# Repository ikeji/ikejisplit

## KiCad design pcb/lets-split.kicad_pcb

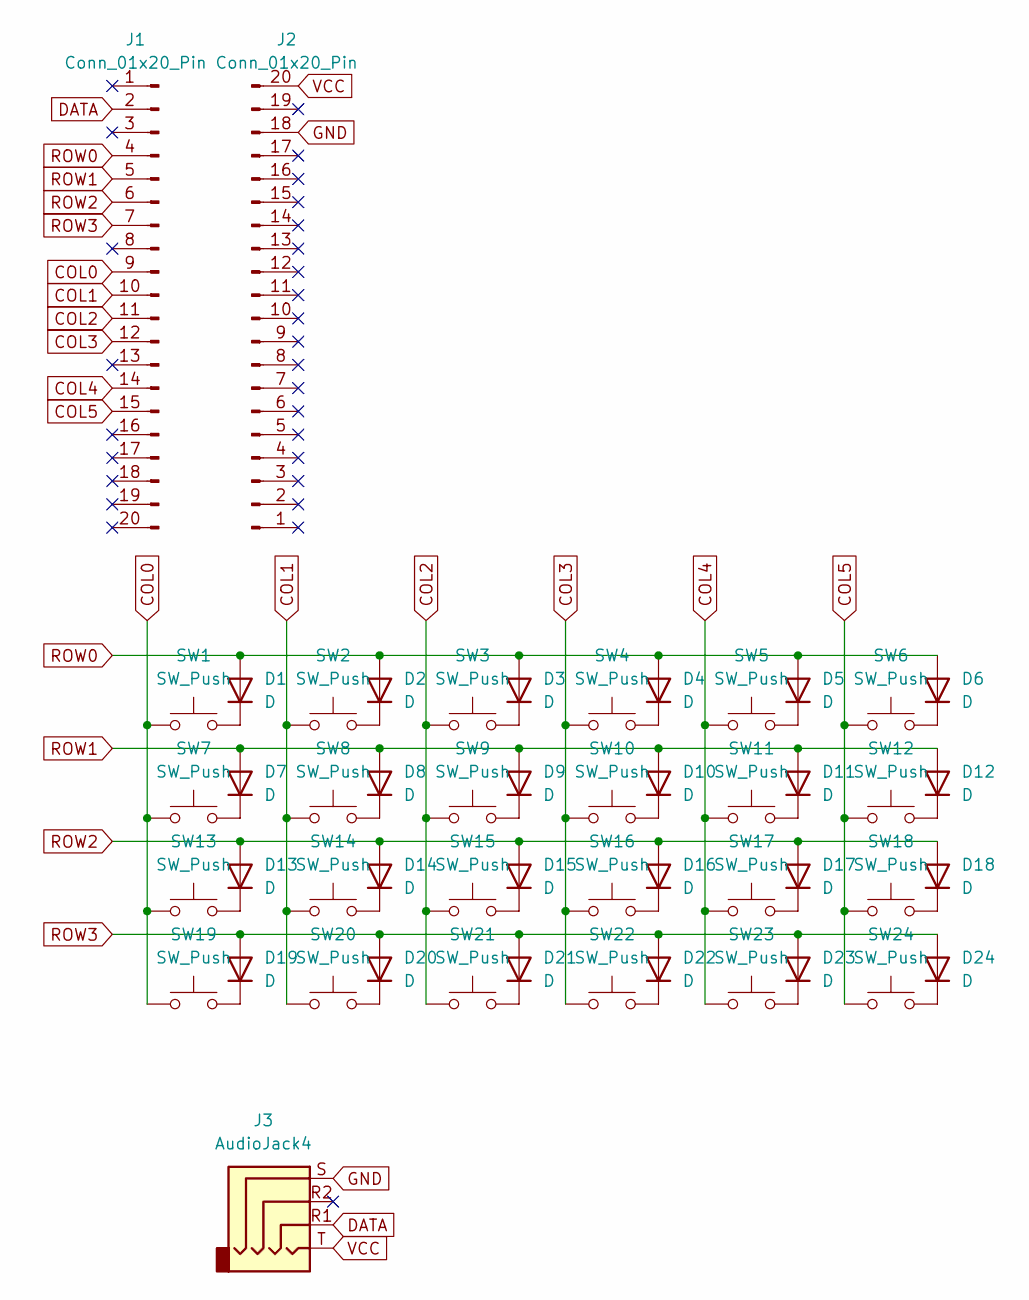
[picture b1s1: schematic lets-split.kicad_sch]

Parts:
D1, D2, D3, D4, D5, D6, D7, D8, D9, D10, D11, D12, D13, D14, D15, D16, D17, D18, D19, D20, D21, D22, D23, D24: D; D_DO-34_SOD68_P7.62mm_Horizontal
J1, J2: Conn_01x20_Pin; PinHeader_1x20_P2.54mm_Vertical
J3: AudioJack4; Jack_3.5mm_PJ320E_Horizontal
SW1, SW2, SW3, SW4, SW5, SW6, SW7, SW8, SW9, SW10, SW11, SW12, SW13, SW14, SW15, SW16, SW17, SW18, SW19, SW20, SW21, SW22, SW23, SW24: SW_Push; SW_Cherry_MX_1.00u_PCB

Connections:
COL0: J1.9, SW1.1, SW7.1, SW13.1, SW19.1
COL1: J1.10, SW2.1, SW8.1, SW14.1, SW20.1
COL2: J1.11, SW3.1, SW9.1, SW15.1, SW21.1
COL3: J1.12, SW4.1, SW10.1, SW16.1, SW22.1
COL4: J1.14, SW5.1, SW11.1, SW17.1, SW23.1
COL5: J1.15, SW6.1, SW12.1, SW18.1, SW24.1
DATA: J1.2, J3.R1
GND: J2.18, J3.S
unnamed: D1.1 (K), SW1.2
unnamed: D2.1 (K), SW2.2
unnamed: D3.1 (K), SW3.2
unnamed: D4.1 (K), SW4.2
unnamed: D5.1 (K), SW5.2
unnamed: D6.1 (K), SW6.2
unnamed: D7.1 (K), SW7.2
unnamed: D8.1 (K), SW8.2
unnamed: D9.1 (K), SW9.2
unnamed: D10.1 (K), SW10.2
unnamed: D11.1 (K), SW11.2
unnamed: D12.1 (K), SW12.2
unnamed: D13.1 (K), SW13.2
unnamed: D14.1 (K), SW14.2
unnamed: D15.1 (K), SW15.2
unnamed: D16.1 (K), SW16.2
unnamed: D17.1 (K), SW17.2
unnamed: D18.1 (K), SW18.2
unnamed: D19.1 (K), SW19.2
unnamed: D20.1 (K), SW20.2
unnamed: D21.1 (K), SW21.2
unnamed: D22.1 (K), SW22.2
unnamed: D23.1 (K), SW23.2
unnamed: D24.1 (K), SW24.2
ROW0: D1.2 (A), D2.2 (A), D3.2 (A), D4.2 (A), D5.2 (A), D6.2 (A), J1.4
ROW1: D7.2 (A), D8.2 (A), D9.2 (A), D10.2 (A), D11.2 (A), D12.2 (A), J1.5
ROW2: D13.2 (A), D14.2 (A), D15.2 (A), D16.2 (A), D17.2 (A), D18.2 (A), J1.6
ROW3: D19.2 (A), D20.2 (A), D21.2 (A), D22.2 (A), D23.2 (A), D24.2 (A), J1.7
VCC: J2.20, J3.T

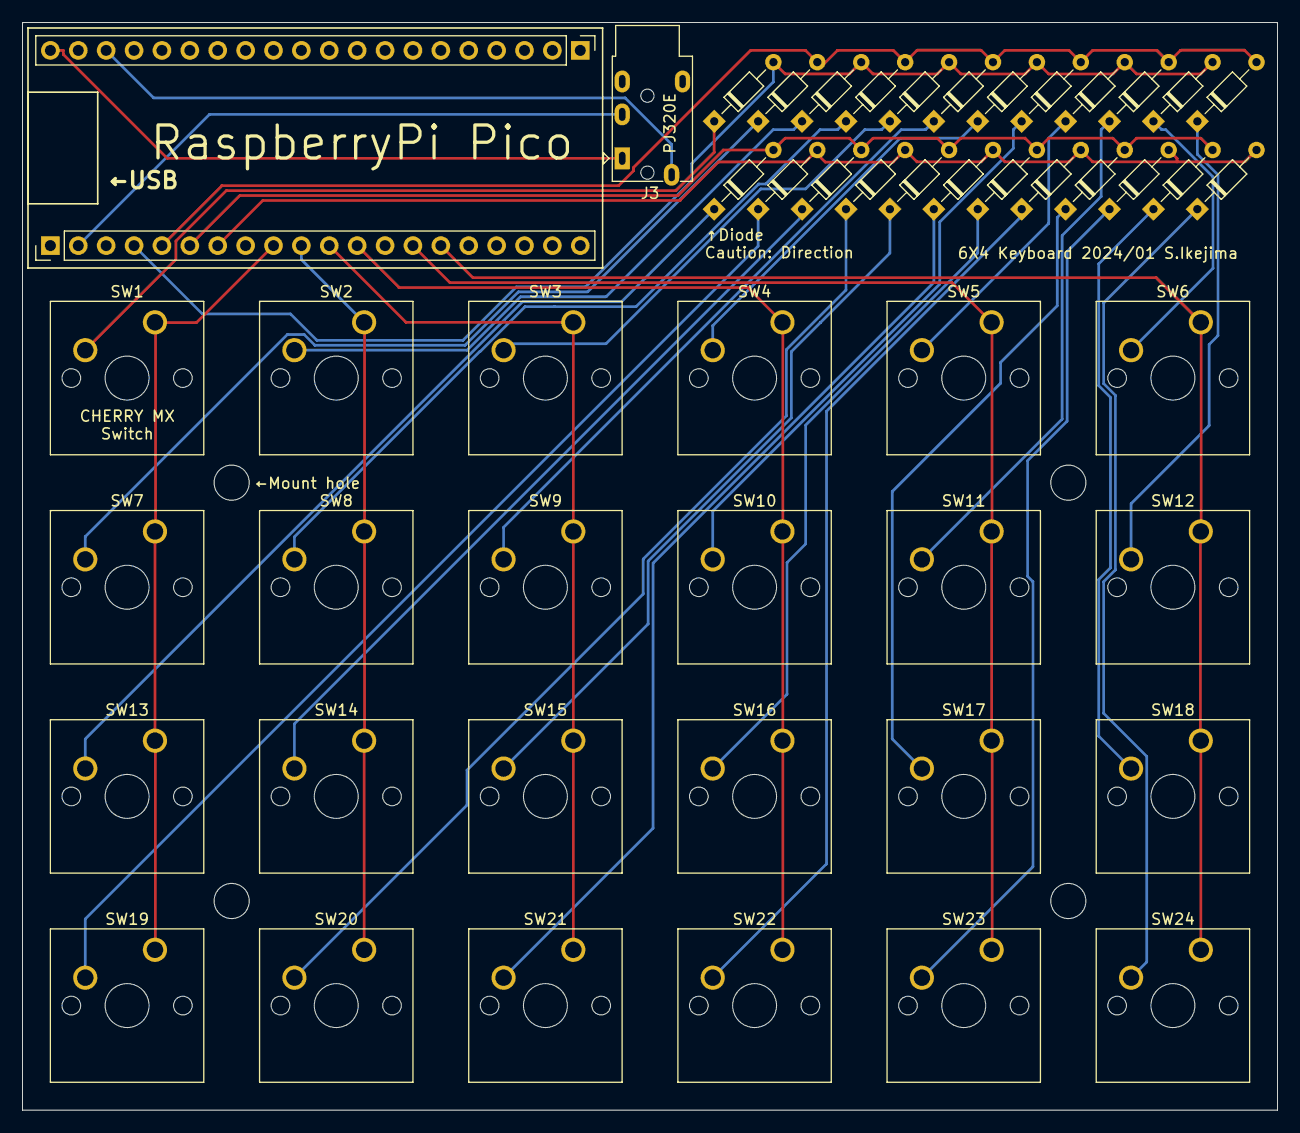
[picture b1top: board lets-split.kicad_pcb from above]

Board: 2 copper layers, 114.3 x 99.1 mm, 55 parts (0 on the bottom side), 37 nets.

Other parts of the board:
REF1, REF2, REF3, REF4: MountingHole_3.2mm_M3

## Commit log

2024-01-25 Initial commit for pcb.
2024-03-02 Order!
2024-09-17 Initial commit firmware.
2025-01-08 Catch up latest kmk firmware.
2025-01-08 Add index.md
